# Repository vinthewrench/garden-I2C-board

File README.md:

Raspberry Pi add on card to that provides isolated I2C, Differential I2C and 1-Wire support.

see the article at https://www.vinthewrench.com/p/raspberry-pi-internet-of-things-part-2a8

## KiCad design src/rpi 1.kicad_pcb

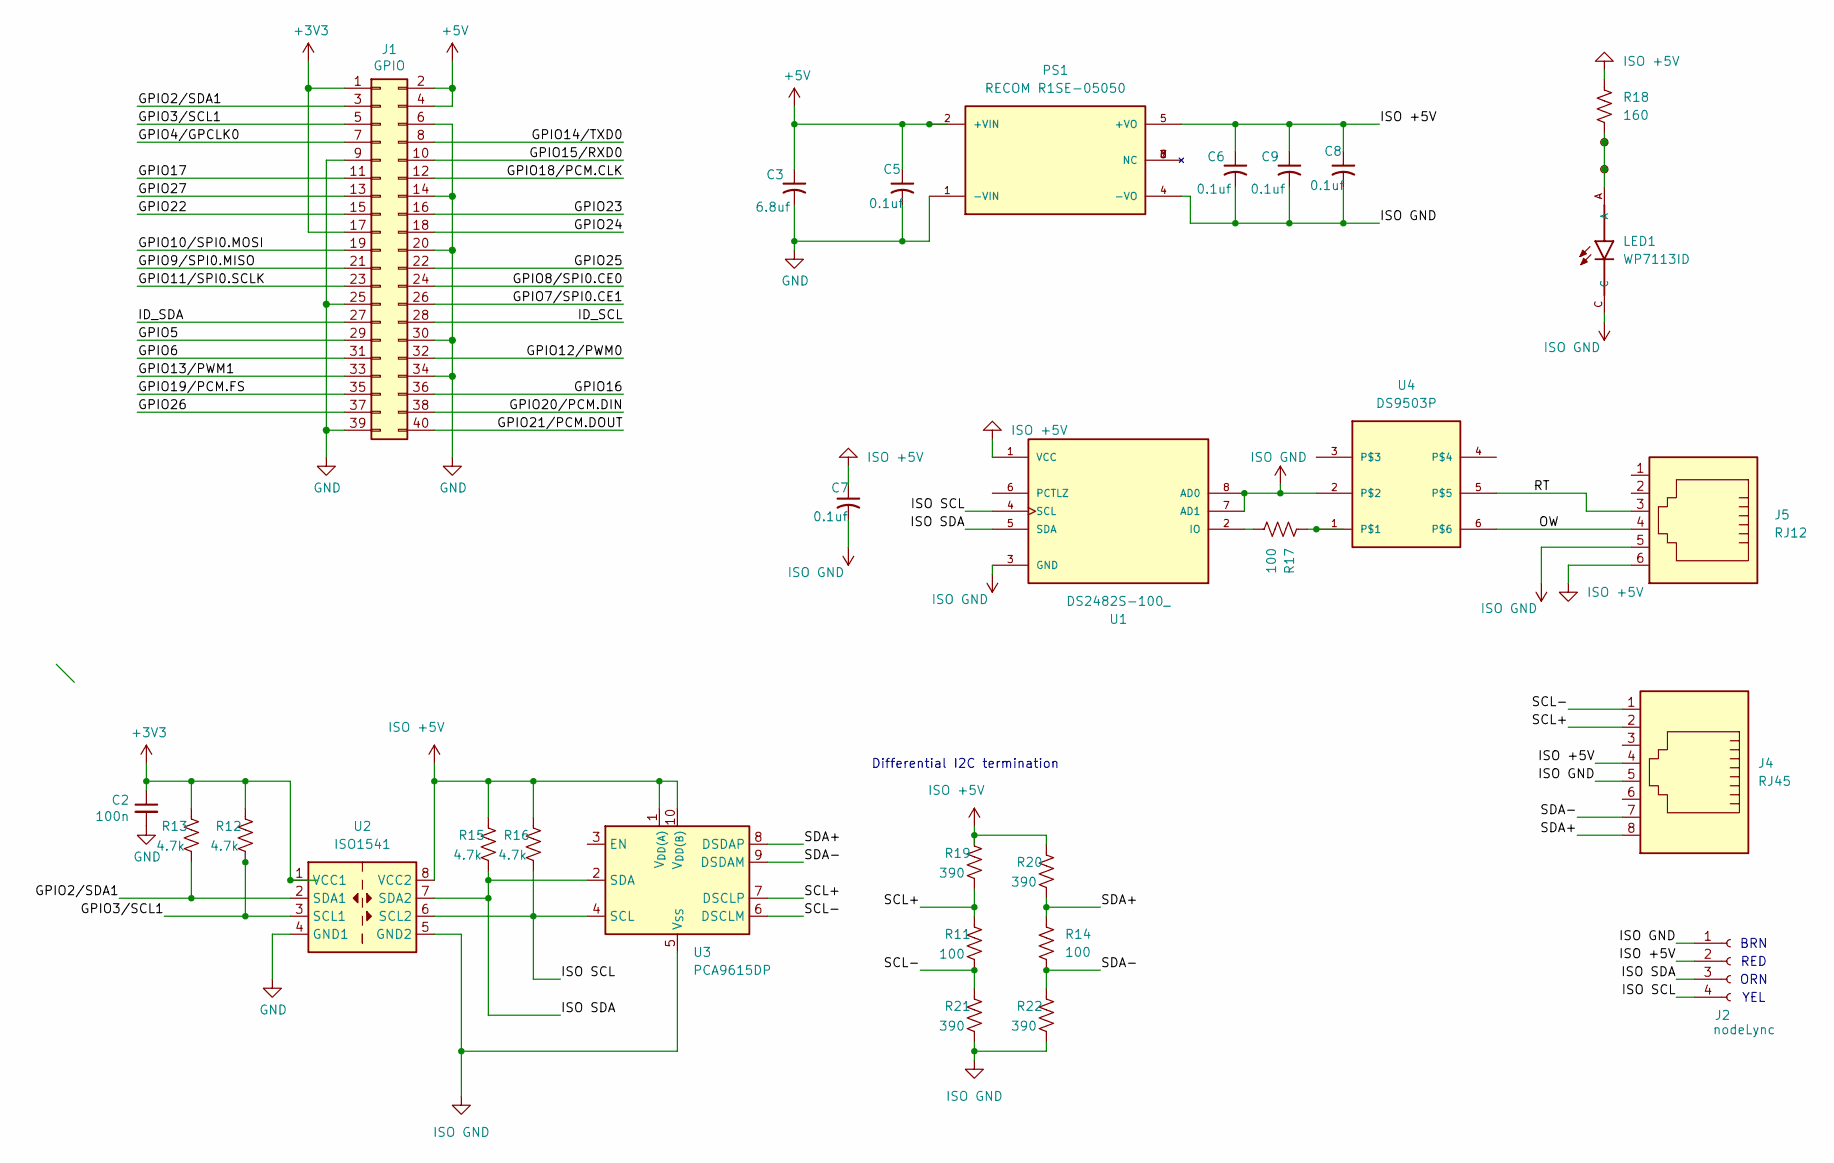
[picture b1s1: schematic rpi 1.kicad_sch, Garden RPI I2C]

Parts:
C2: 100n; C_Disc_D5.0mm_W2.5mm_P2.50mm
C3: 6.8uf; C_Radial_D8.0mm_H11.5mm_P3.50mm
C5, C6, C7, C8, C9: 0.1uf; C_Disc_D5.0mm_W2.5mm_P2.50mm
J1: GPIO; PinSocket_2x20_P2.54mm_Vertical
J2: nodeLync; PinHeader_1x04_P2.54mm_Horizontal
J4: RJ45; RJ45_Amphenol_54602-x08_Horizontal
J5: RJ12; RJ12_Amphenol_54601-x06_Horizontal
LED1: WP7113ID; LED_WP7113ID
PS1: RECOM R1SE-05050; SSO-8_6.7x9.8mm_P2.54mm_Clearance8mm; PARTREV September 23, 2022
R11, R14, R17: 100; R_Axial_DIN0204_L3.6mm_D1.6mm_P5.08mm_Horizontal
R12, R13, R15, R16: 4.7k; R_Axial_DIN0204_L3.6mm_D1.6mm_P5.08mm_Horizontal
R18: 160; R_Axial_DIN0204_L3.6mm_D1.6mm_P5.08mm_Horizontal
R19, R20, R21, R22: 390; R_Axial_DIN0204_L3.6mm_D1.6mm_P5.08mm_Horizontal
TP1, TP2: TestPoint_Small; TestPoint_Pad_1.0x1.0mm
U1: DS2482S-100_; SOIC-8_3.9x4.9mm_P1.27mm
U2: ISO1541; SOIC-8_3.9x4.9mm_P1.27mm
U3: PCA9615DP; TSSOP-10_3x3mm_P0.5mm
U4: DS9503P; TSOC-6_3.76x3.94mm_P1.27mm

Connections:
+3V3: C2.1, J1.1, J1.17, R12.1, R13.1, U2.1 (VCC1)
+5V: C3.1, C5.1, J1.2, J1.4, PS1.2 (+VIN)
/GPIO2/SDA1: J1.3, R13.2, U2.2 (SDA1)
/GPIO3/SCL1: J1.5, R12.2, U2.3 (SCL1)
/GPIO4/GPCLK0: J1.7
/GPIO5: J1.29
/GPIO6: J1.31
/GPIO7/SPI0.CE1: J1.26
/GPIO8/SPI0.CE0: J1.24
/GPIO9/SPI0.MISO: J1.21
/GPIO10/SPI0.MOSI: J1.19
/GPIO11/SPI0.SCLK: J1.23
/GPIO12/PWM0: J1.32
/GPIO13/PWM1: J1.33
/GPIO14/TXD0: J1.8
/GPIO15/RXD0: J1.10
/GPIO16: J1.36
/GPIO17: J1.11
/GPIO18/PCM.CLK: J1.12
/GPIO19/PCM.FS: J1.35
/GPIO20/PCM.DIN: J1.38
/GPIO21/PCM.DOUT: J1.40
/GPIO22: J1.15
/GPIO23: J1.16
/GPIO24: J1.18
/GPIO25: J1.22
/GPIO26: J1.37
/GPIO27: J1.13
/ID_SCL: J1.28
/ID_SDA: J1.27
/ISO SCL: J2.4, R16.2, U1.4 (SCL), U2.6 (SCL2), U3.4 (SCL)
/ISO SDA: J2.3, R15.2, U1.5 (SDA), U2.7 (SDA2), U3.2 (SDA)
/OW: J5.4, U4.6
/RT: J5.3, U4.5
/SCL+: J4.2, R11.1, R19.2, U3.7 (DSCLP)
/SCL-: J4.1, R11.2, R21.1, U3.6 (DSCLM)
/SDA+: J4.8, R14.1, R20.2, U3.8 (DSDAP)
/SDA-: J4.7, R14.2, R22.1, U3.9 (DSDAM)
GND: C2.2, C3.2, C5.2, J1.6, J1.9, J1.14, J1.20, J1.25, J1.30, J1.34, J1.39, PS1.1 (-VIN), U2.4 (GND1)
ISO +5V: C6.1, C7.1, C8.1, C9.1, J2.2, J4.4, J5.6, PS1.5 (+VO), R15.1, R16.1, R18.1, R19.1, R20.1, U1.1 (VCC), U2.8 (VCC2), U3.1 (V_{DD(A)}), U3.10 (V_{DD(B)})
ISO GND: C6.2, C7.2, C8.2, C9.2, J2.1, J4.5, J5.5, LED1.C, PS1.4 (-VO), R21.2, R22.2, U1.3 (GND), U1.7 (AD1), U1.8 (AD0), U2.5 (GND2), U3.5 (V_{SS}), U4.2
unnamed: LED1.A, R18.2, TP1.1, TP2.1
unnamed: R17.2, U1.2 (IO)
unnamed: R17.1, U4.1

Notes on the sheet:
BRN
Differential I2C termination
YEL
RED
ORN

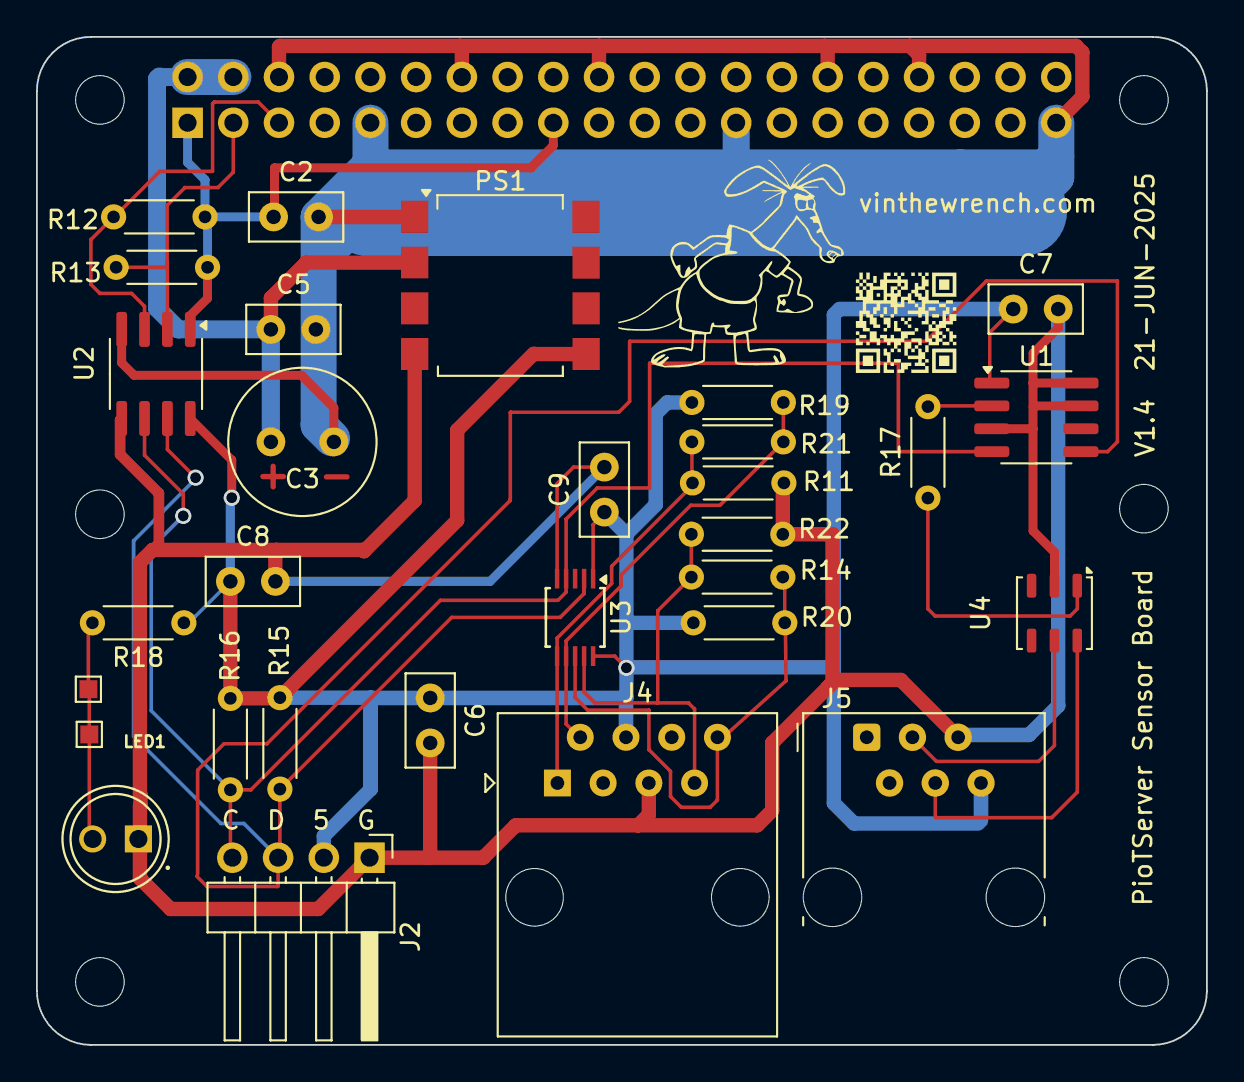
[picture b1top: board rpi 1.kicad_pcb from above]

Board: 2 copper layers, 65.0 x 56.0 mm, 36 parts (1 on the bottom side), 18 nets.

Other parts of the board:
MH1, MH2, MH3, MH4: MountingHole_2.7mm_M2.5
X: LOGO; aard1

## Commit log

2025-06-21 first checkin
2025-06-21 add schematic pdf
2025-06-22 added PDF of article
